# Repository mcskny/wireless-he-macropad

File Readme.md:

> **Separate transport profiles (experimental):** C6 0.1.6 and Studio 0.1.4 keep BLE and ESP-NOW layer settings separately, copying prior shared settings on first migration. Separate key assignments across mode switches were verified on the current hardware. Hall calibration remains shared.

> **6 November 2026:** Studio supports configuring C6 lighting, selecting layers and writing supported per-layer HID assignments over encrypted BLE. Hardware checks confirmed lighting changes on two layers and an H assignment that survived a C6 restart. Three paired-slot names are locally editable aliases, not automatically retrieved host names. BLE sensor telemetry and automatic synchronization between C6 and S3 are not implemented; a solid lighting color also persisted across a restart with Studio closed. Other hosts need further testing.

# Wireless HE Macropad

A wireless, 12-key Hall-effect macropad built around a custom PCB, an ESP32-C6 sender, an ESP32-S3 USB receiver, and a native macOS companion app.

The project explores analog key travel, configurable actuation, per-layer actions, responsive lighting, and power-conscious wireless operation. It is an **active hardware and firmware prototype**, not a finished commercial product.

## At a glance

- **12 analog Hall-effect keys**, arranged in three columns and four rows.
- A separate mechanical **layer button**, four layer indicator positions, and a rotary encoder in the design.
- **ESP32-C6 → ESP-NOW → ESP32-S3 → USB** for the current wireless test system.
- Direct **C6-to-host BLE HID** is integrated and keyboard output was confirmed on a Mac. Bond persistence and automatic reconnection still need a complete restart and mode-switch test.
- A custom PCB with DRV5055 sensors, a 16-channel multiplexer, and an external 12-bit ADC.
- Per-key lighting driven by a chain of 12 addressable LEDs.
- **Wireless HE Studio**, a native macOS app with live telemetry, calibration, interactive 2D/3D views, layers, and lighting controls.

## Gallery

<table>
<tr>
<td align="center"><br><b>Enclosure and layout</b></td>
<td align="center"><br><b>Custom PCB</b></td>
</tr>
<tr>
<td align="center"><br><b>Studio · layers and key assignments</b></td>
<td align="center"><br><b>Studio · lighting and 3D preview</b></td>
</tr>
</table>

The enclosure and PCB images are renders; Studio screenshots illustrate the interface and may not show its latest revision.

## How it works

Each key moves a magnet past a Hall sensor. The sensor's analog output is sampled and converted into a calibrated position, allowing the prototype to react to key travel rather than just an on/off switch.

```text
12 × DRV5055 sensors → CD74HC4067 multiplexer → MCP3202 ADC
                                                    │
                                           ESP32-C6 macropad
                                                    │ ESP-NOW
                                                    ▼
Mac / computer ← USB HID + serial telemetry ← ESP32-S3 dongle
        │                                           ▲
        └──── Studio configuration and live lighting ┘
```

The repository contains both the **current C6/S3 test bridge** and separate, evolving product-firmware projects. They are not interchangeable builds and do not necessarily use the same pin assignments.

## What works today

The following describes the test setup and the specific behavior observed, as of **5 November 2026**. A successful test of one action does not mean every combination has been validated.

| Area | Observed on the prototype | Still to do |
|---|---|---|
| Sensing | All 12 channels appeared in Studio; individual calibration, channel mapping, and live key movement were checked. | Long-run stability, cross-channel effects, physical travel measurement, and full calibration validation. |
| Wireless link | C6 → S3 → Mac telemetry works; Studio displays scan, submission, reception, and sequence-gap counters. | Reduce active-mode gaps, measure latency and range, and add authenticated pairing/encryption. |
| Direct BLE | C6 paired with a Mac and typed using a saved profile; Layer + KEY 0 switched transport and the transition effects were checked. | Validate persisted bonding across reboot and transport changes, BLE disconnect release, other hosts, latency, and power. |
| USB keyboard | Layer-specific keyboard actions and volume-down HID were tested on a Mac. A saved layer survived an S3 reconnect; output also worked with Studio closed. | More host/shortcut tests, disconnect recovery, and NKRO. The current keyboard report is 6KRO. |
| Hall behaviors | Rapid Trigger retriggering was tested with a partially released key. SOCD's last-pressed priority and return to the held key were also tested. | Wider sensitivity, multi-key, and long-duration hardware tests; two-stage behavior needs a physical test. |
| Lighting | All 12 LEDs lit. Live layer/effect synchronization, rainbow or snake color behavior, and virtual-key ripple triggering were checked. Sweep turn-off and ripple stopping were also checked physically. | Validate the complete effect set and persistence; lighting configuration is currently sent live rather than stored permanently on the device. |
| Power policy | Idle sensor scans and software-controlled MOSFET duty cycling were observed; the app displays commanded gate on-time. | Measure rail voltage, startup/settling, backfeed, actual current, and battery life. |
| Mac app | Live sensor values, 2D/3D views, layer controls, local profiles, and the device write path are available. Blender's move, rotate, and scale actions were tested. | Complete and validate all target-app actions, accessibility, long-term performance, and hardware integration. |
| Mechanical | A 3D model, PCB design, and enclosure renders exist. | Manufacture and validate the plate, case fit, and final assembly. |

The percentage in the graphic is a **manually reviewed, equally weighted checklist estimate**. Some items overlap; it is not a measurement of remaining work, reliability, or product readiness. See the [compact progress grid](Docs/progress/project-progress-grid-en.png) for the item index.

## Wireless HE Studio

Studio is a native **SwiftUI / AppKit / SceneKit** macOS application. Its current features include:

- A live ADC graph, raw channel diagnostics, channel remapping, per-key calibration, and idle-noise measurements.
- Interactive 2D and 3D views, key motion, and an exploded component view based on the project model.
- Four layers with keyboard/media actions, traditional thresholds, Rapid Trigger, SOCD, and local profile storage.
- Lighting previews and live control of effects such as static, breathing, wave, sweep, reactive, ripple, starlight, rainbow, and snake.
- Live rate and power-policy telemetry, including **commanded GPIO on-time** rather than a measured power figure.
- Turkish and English interface options, local backup, and sensor-session logs.

Studio includes 13 starter profiles covering creative applications and games. The 156 preset entries include direct mappings and suggested shortcuts that may need assignment in the target application; mapping and real application validation are distinct. The UI identifies these assignments. A mapped output does not prove the target application accepts it or that its shortcuts match the user's settings. Encoder actions and native analog gamepad output are not yet implemented end to end.

Studio writes supported actions for the **selected layer** to the S3. Calibration endpoints and supported Hall settings are included; local profile storage and device storage are distinct. Verify the target layer and assigned shortcuts before writing.

## Sampling and power experiments

The current test policy scans at **100 Hz while idle**, with a **1 kHz active target** after detected movement. Idle radio updates are targeted at 10 Hz without Studio or 100 Hz while Studio is connected; active transmission targets 1 kHz. The observed values in Studio are measurements, not guarantees of those targets.

In one active test the C6 reported roughly **983 scans/s** and **858 radio submissions/s**. These are short observations under specific conditions; submissions, received packets, and end-to-end input latency are different measurements. Sequence gaps can arise in scheduling, radio transmission, buffering, or USB.

With the experimental MOSFET build, the idle test showed approximately **13% commanded gate on-time**. Active-mode duty cycling with a 600 µs startup wait reduced a trial to about **620 scans/s**, so that experiment was reverted: the current active mode keeps the analog rail commanded on. GPIO timing does **not** establish the actual rail voltage, energy savings, or battery life. No power-saving multiplier is claimed.

## Hardware overview

| Component | Role |
|---|---|
| 12 × DRV5055A4 | Analog Hall sensors |
| CD74HC4067 | 16-channel analog multiplexer |
| MCP3202 | 12-bit external ADC |
| XIAO ESP32-C6 | Current wireless sender test board |
| ESP32-S3 | USB receiver and HID test board |
| 12 × SK6812MINI | Addressable key lighting |
| Mechanical switch | Layer button; current test wiring uses D7 to GND |
| Rotary encoder and four indicators | Designed controls; full hardware integration remains in progress |

The **test-bridge** C6 wiring uses D0–D3 for multiplexer selection, D4 for ADC chip select, D8–D10 for SPI, D6/GPIO16 for LED data, D5/GPIO23 for the optional active-low analog power gate, and D7/GPIO17 for the layer button. Check the [bridge documentation](examples/c6_s3_sensor_bridge/README.md), the actual board, and the schematic before connecting or powering anything. These pins are **not** a promise about the separate product firmware.

## Repository layout

| Path | Contents |
|---|---|
| [`Hardware/Kicad/`](Hardware/Kicad/) | PCB and schematic source files |
| [`Firmware/macropad-sender/`](Firmware/macropad-sender/) | Developing C6 product firmware |
| [`Firmware/dongle-receiver/`](Firmware/dongle-receiver/) | Developing S3 product firmware |
| [`Firmware/shared/`](Firmware/shared/) | Shared firmware modules and tests |
| [`examples/c6_s3_sensor_bridge/`](examples/c6_s3_sensor_bridge/) | Current C6/S3 wireless prototype and HID bridge |
| [`examples/c6_ble_hid_lab/`](examples/c6_ble_hid_lab/) | Isolated, buildable BLE HID transport experiment (separate from the integrated C6 build) |
| [`examples/macropad_12_idf/mac_app/`](examples/macropad_12_idf/mac_app/) | Wireless HE Studio macOS app |
| [`examples/lighting_espnow_lab/`](examples/lighting_espnow_lab/) | Lighting engine and protocol experiments |
| [`examples/crossover_analog/`](examples/crossover_analog/) | Earlier CrossOver analog-controller experiment |
| [`tools/progress.py`](tools/progress.py) | Generates the Turkish project progress map |

The earlier Assetto Corsa steering/throttle/brake experiment used a **wired sensor platform and a CrossOver virtual-controller bridge**. It does not demonstrate native analog gamepad output from the current S3 dongle.

## Build and test

The prototype firmware has been built with the project's **ESP-IDF 6.1** environment. The following examples build only; select the correct board, port, wiring, and configuration before flashing.

```sh
# C6 BLE + ESP-NOW test configuration
cd examples/c6_s3_sensor_bridge/c6
idf.py -B build-ble -D SDKCONFIG=sdkconfig.ble build
```

```sh
# S3 composite receiver — run from the repository root
cd examples/c6_s3_sensor_bridge/s3_composite
idf.py set-target esp32s3
idf.py build
```

The **experimental MOSFET build** uses a separate power configuration and requires the correct physical switching circuit; see the [bridge README](examples/c6_s3_sensor_bridge/README.md) before using it. The standard build should not be assumed to have the same gate configuration as the test board.

For the macOS app, see the [Studio README](examples/macropad_12_idf/mac_app/README.md). The current local build script targets macOS 26 and expects a configured ESP-IDF Python environment; it is not yet a signed, notarized general distribution.

## Known limitations

- ESP-NOW uses broadcast frames without authenticated encryption; CRC and source MAC checks do not authenticate senders. BLE encrypts links with bonded Just Works pairing, which does not provide MITM authentication.
- The S3 reports up to six ordinary keyboard keys at once; native analog gamepad output and physical encoder HID are unfinished.
- Some preset actions require explicit shortcut setup in the target program. Encoder presets and game-mode previews must not be mistaken for completed hardware behavior.
- The MOSFET status in Studio reports software commands. Actual sensor-rail behavior and power consumption still need electrical measurement.
- Hardware, firmware, app, and documentation are evolving; verify the specific test configuration before relying on a feature.

## Versioning and releases

C6 firmware, S3 firmware, and Studio use separate version numbers and GitHub releases. See [release notes](releases/CHANGELOG.md), [versions](releases/versions.json). Published tags are immutable. Initial releases are pre-releases; the Studio source currently has machine-specific runtime paths, so a portable binary is not claimed.

## License

This project is licensed under the [GNU General Public License, version 3](LICENSE) (GPL-3.0-only). Third-party components retain their own licenses.

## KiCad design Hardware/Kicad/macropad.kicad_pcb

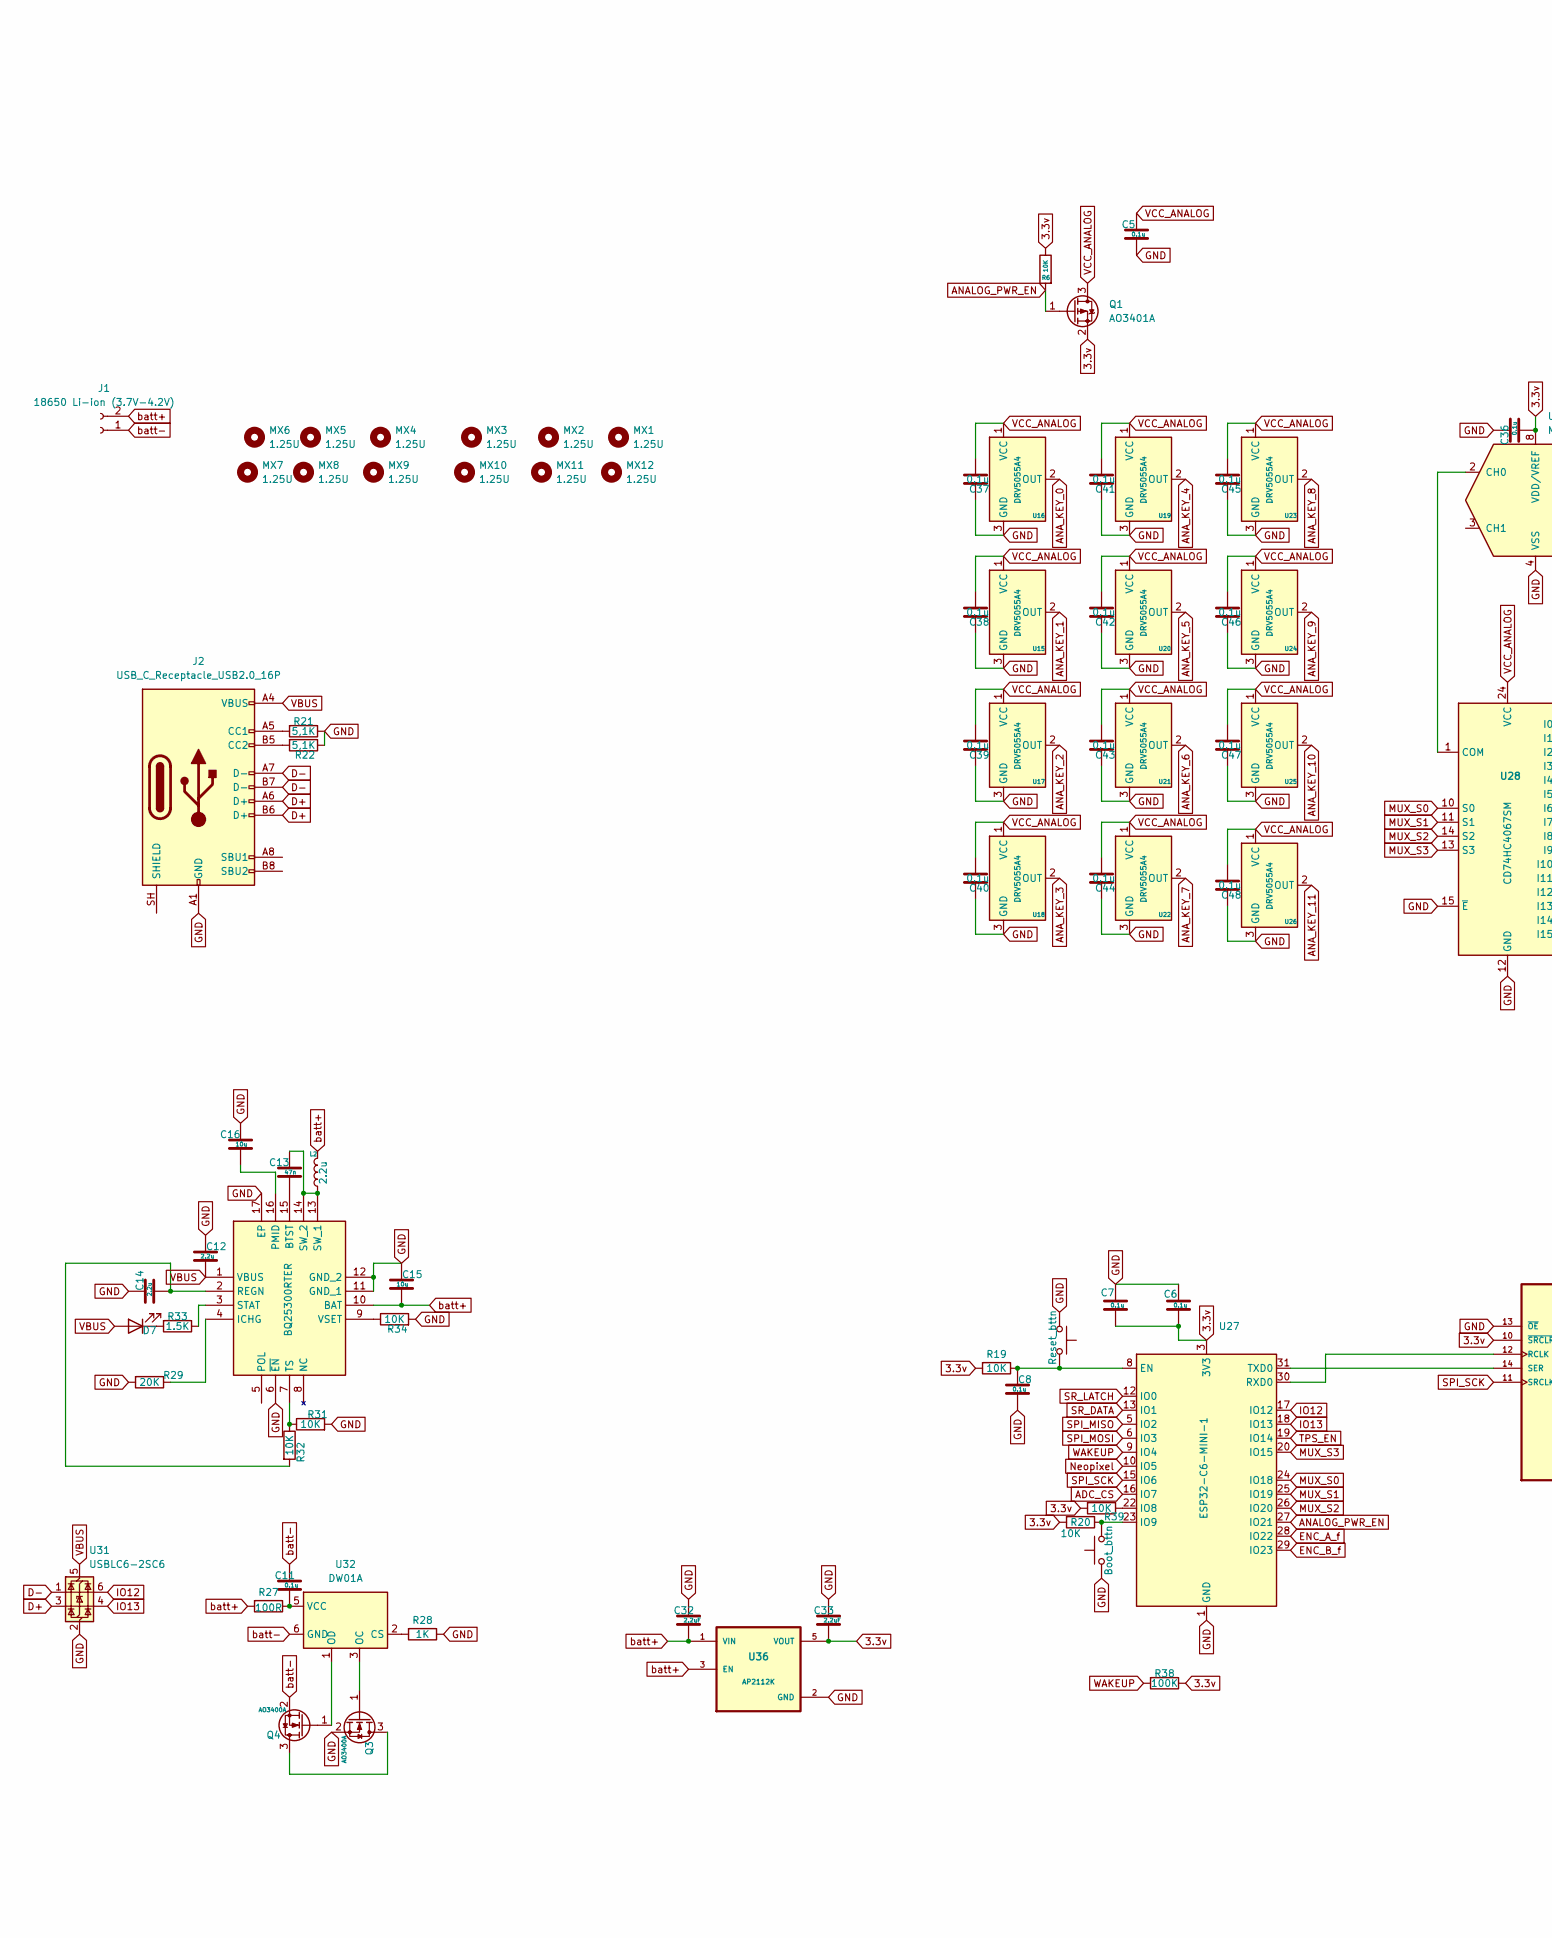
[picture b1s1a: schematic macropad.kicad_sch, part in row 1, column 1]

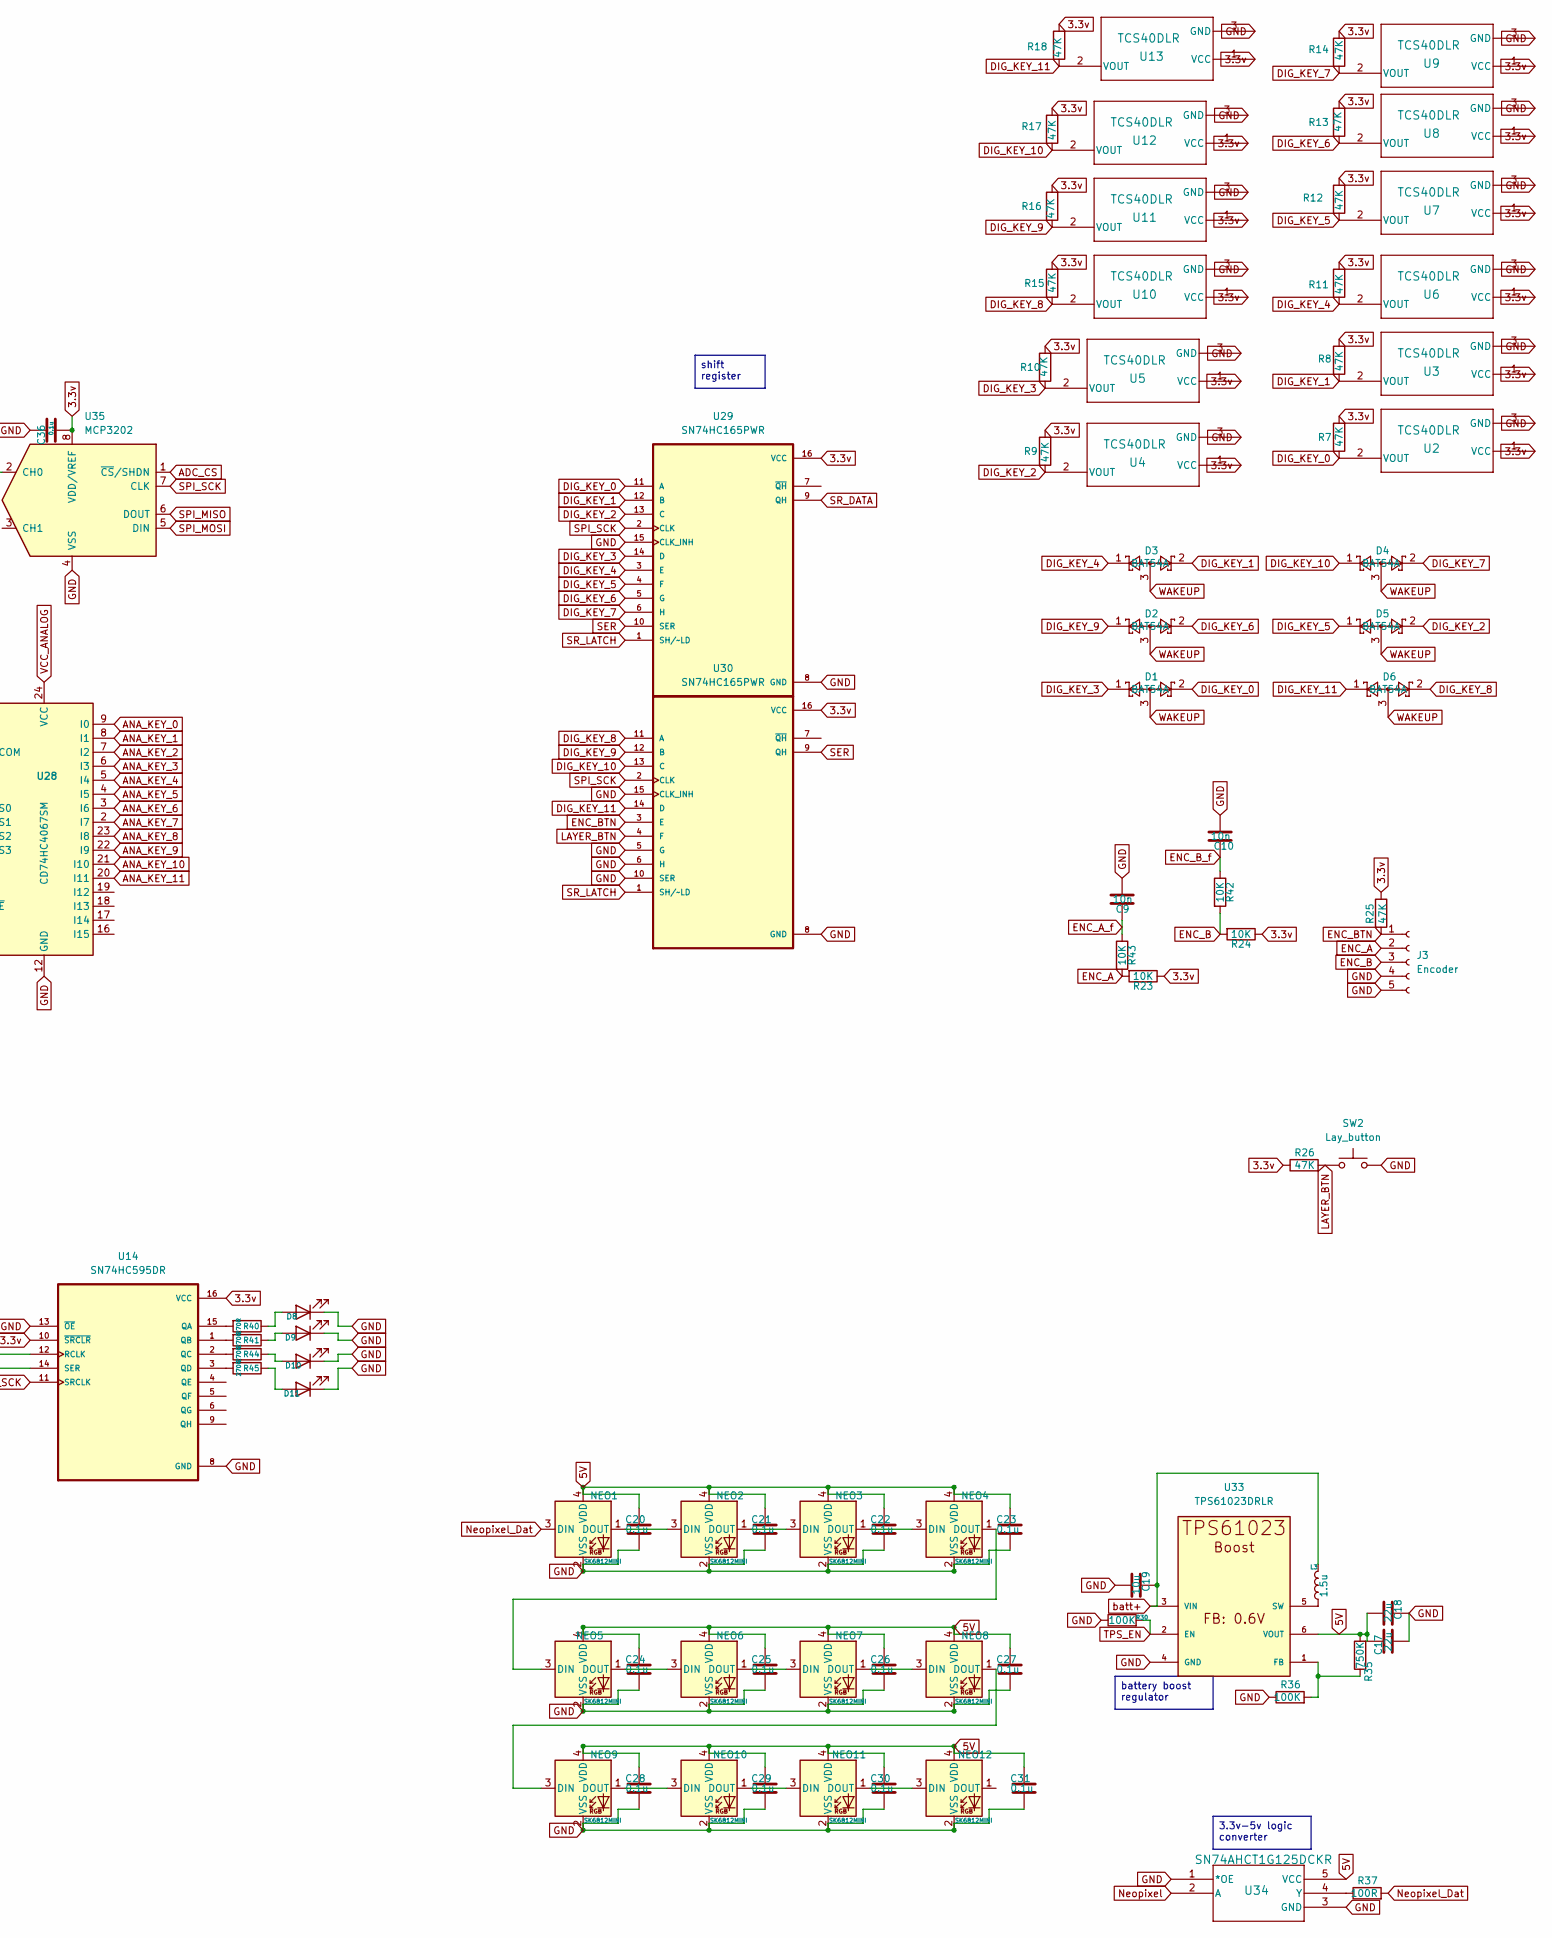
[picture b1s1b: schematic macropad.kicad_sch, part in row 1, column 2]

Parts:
C5, C6, C7, C8, C11, C20, C21, C22, C23, C24, C25, C26, C27, C28, C29, C30, C31, C36, C37, C38, C39, C40, C41, C42, C43, C44, C45, C46, C47, C48: 0.1u; C_0603_1608Metric_Pad1.08x0.95mm_HandSolder
C9, C10: 10n; C_0603_1608Metric_Pad1.08x0.95mm_HandSolder
C12, C14: 2.2u; C_0603_1608Metric_Pad1.08x0.95mm_HandSolder
C13: 47n; C_0603_1608Metric_Pad1.08x0.95mm_HandSolder
C15, C16: 10u; C_0805_2012Metric_Pad1.18x1.45mm_HandSolder
C17, C18: 22u; C_0603_1608Metric_Pad1.08x0.95mm_HandSolder
C19: 10u; C_0603_1608Metric_Pad1.08x0.95mm_HandSolder
C32, C33: 2.2uF; C_0603_1608Metric_Pad1.08x0.95mm_HandSolder
D1, D2, D3, D4, D5, D6: BAT54A; SOT-23_Handsoldering
D7, D8, D9, D10, D11: LED; LED_0603_1608Metric
J1: 18650 Li-ion (3.7V-4.2V); 648102131822
J2: USB_C_Receptacle_USB2.0_16P; USB_C_Receptacle_GCT_USB4110
J3: Encoder; SM04BPASS1TBTLFSN
L2: 2.2u; SRN4030HA2R2Y
L3: 1.5u; INDC2520X100N
MX1, MX2, MX3, MX4, MX5, MX6, MX7, MX8, MX9, MX10, MX11, MX12: 1.25U; switchsocket
NEO1, NEO2, NEO3, NEO4, NEO5, NEO6, NEO7, NEO8, NEO9, NEO10, NEO11, NEO12: SK6812MINI; LED_SK6812MINI_PLCC4_3.5x3.5mm_P1.75mm
Q1: AO3401A; SOT-23_Handsoldering
Q3, Q4: AO3400A; SOT-23
R6, R19, R20, R23, R24, R31, R32, R34, R39, R42, R43: 10K; R_0603_1608Metric_Pad0.98x0.95mm_HandSolder
R7, R8, R9, R10, R11, R12, R13, R14, R15, R16, R17, R18, R25, R26: 47K; R_0603_1608Metric_Pad0.98x0.95mm_HandSolder
R21, R22: 5,1K; R_0603_1608Metric_Pad0.98x0.95mm_HandSolder
R27, R37: 100R; R_0603_1608Metric_Pad0.98x0.95mm_HandSolder
R28: 1K; R_0603_1608Metric_Pad0.98x0.95mm_HandSolder
R29: 20K; R_0603_1608Metric_Pad0.98x0.95mm_HandSolder
R30, R36, R38: 100K; R_0603_1608Metric_Pad0.98x0.95mm_HandSolder
R33: 1.5K; R_0603_1608Metric_Pad0.98x0.95mm_HandSolder
R35: 750K; R_0603_1608Metric_Pad0.98x0.95mm_HandSolder
R40, R41, R44, R45: 270R; R_0603_1608Metric_Pad0.98x0.95mm_HandSolder
SW1: Boot_bttn; SW_Push_1P1T_NO_CK_KMR2
SW2: Lay_button; SW_Cherry_MX_1.00u_PCB
SW3: Reset_bttn; SW_Push_1P1T_NO_CK_KMR2
U2, U3, U4, U5, U6, U7, U8, U9, U10, U11, U12, U13: TCS40DLR; SOT-23_Handsoldering
U14: SN74HC595DR; SOIC127P600X175-16N
U15, U16, U17, U18, U19, U20, U21, U22, U23, U24, U25, U26: DRV5055A4; SOT-23_Handsoldering
U27: ESP32-C6-MINI-1
U28: CD74HC4067SM; SSOP-24_5.3x8.2mm_P0.65mm
U29, U30: SN74HC165PWR; SOP65P640X120-16N
U31: USBLC6-2SC6; SOT-23-6
U32: DW01A; SOT-23-6
U33: TPS61023DRLR; SOT563-ORI
U34: SN74AHCT1G125DCKR; DCK5
U35: MCP3202; SOIC-8_3.9x4.9mm_P1.27mm
U36: AP2112K; SOT95P285X140-5N; PARTREV 2-2
Z1: BQ25300RTER; QFN50P300X300X80-17N-D; Mouser Part Number 595-BQ25300RTER

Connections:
3.3v: C6.2, C7.2, C33.2, C36.2, Q1.2 (S), R6.1, R7.2, R8.2, R9.2, R10.2, R11.2, R12.2, R13.2, R14.2, R15.2, R16.2, R17.2, R18.2, R19.2, R20.2, R23.1, R24.1, R25.1, R26.1, R38.1, R39.2, U2.1 (VCC), U3.1 (VCC), U4.1 (VCC), U5.1 (VCC), U6.1 (VCC), U7.1 (VCC), U8.1 (VCC), U9.1 (VCC), U10.1 (VCC), U11.1 (VCC), U12.1 (VCC), U13.1 (VCC), U14.10 (~SRCLR), U14.16 (VCC), U27.3 (3V3), U29.16 (VCC), U30.16 (VCC), U35.8 (VDD/VREF), U36.5 (VOUT)
5V: C17.1, C18.2, C20.1, C21.1, C22.1, C23.1, C24.1, C25.1, C26.1, C27.1, C28.1, C29.1, C30.1, C31.1, NEO1.4 (VDD), NEO2.4 (VDD), NEO3.4 (VDD), NEO4.4 (VDD), NEO5.4 (VDD), NEO6.4 (VDD), NEO7.4 (VDD), NEO8.4 (VDD), NEO9.4 (VDD), NEO10.4 (VDD), NEO11.4 (VDD), NEO12.4 (VDD), R35.2, U33.6 (VOUT), U34.5 (VCC)
ADC_CS: U27.16 (IO7), U35.1 (~CS/SHDN)
ANALOG_PWR_EN: Q1.1 (G), R6.2, U27.27 (IO21)
ANA_KEY_0: U16.2 (OUT), U28.9 (I0)
ANA_KEY_1: U15.2 (OUT), U28.8 (I1)
ANA_KEY_2: U17.2 (OUT), U28.7 (I2)
ANA_KEY_3: U18.2 (OUT), U28.6 (I3)
ANA_KEY_4: U19.2 (OUT), U28.5 (I4)
ANA_KEY_5: U20.2 (OUT), U28.4 (I5)
ANA_KEY_6: U21.2 (OUT), U28.3 (I6)
ANA_KEY_7: U22.2 (OUT), U28.2 (I7)
ANA_KEY_8: U23.2 (OUT), U28.23 (I8)
ANA_KEY_9: U24.2 (OUT), U28.22 (I9)
ANA_KEY_10: U25.2 (OUT), U28.21 (I10)
ANA_KEY_11: U26.2 (OUT), U28.20 (I11)
D+: J2.A6 (D+), J2.B6 (D+), U31.3 (I/O2)
D-: J2.A7 (D-), J2.B7 (D-), U31.1 (I/O1)
DIG_KEY_0: D1.2, R7.1, U2.2 (VOUT), U29.11 (A)
DIG_KEY_1: D3.2, R8.1, U3.2 (VOUT), U29.12 (B)
DIG_KEY_2: D5.2, R9.1, U4.2 (VOUT), U29.13 (C)
DIG_KEY_3: D1.1, R10.1, U5.2 (VOUT), U29.14 (D)
DIG_KEY_4: D3.1, R11.1, U6.2 (VOUT), U29.3 (E)
DIG_KEY_5: D5.1, R12.1, U7.2 (VOUT), U29.4 (F)
DIG_KEY_6: D2.2, R13.1, U8.2 (VOUT), U29.5 (G)
DIG_KEY_7: D4.2, R14.1, U9.2 (VOUT), U29.6 (H)
DIG_KEY_8: D6.2, R15.1, U10.2 (VOUT), U30.11 (A)
DIG_KEY_9: D2.1, R16.1, U11.2 (VOUT), U30.12 (B)
DIG_KEY_10: D4.1, R17.1, U12.2 (VOUT), U30.13 (C)
DIG_KEY_11: D6.1, R18.1, U13.2 (VOUT), U30.14 (D)
ENC_A: J3.2, R23.2, R43.2
ENC_A_f: C9.1, R43.1, U27.28 (IO22)
ENC_B: J3.3, R24.2, R42.2
ENC_BTN: J3.1, R25.2, U30.3 (E)
ENC_B_f: C10.1, R42.1, U27.29 (IO23)
GND: C5.2, C6.1, C7.1, C8.1, C9.2, C10.2, C12.2, C14.2, C15.2, C16.2, C17.2, C18.1, C19.2, C20.2, C21.2, C22.2, C23.2, C24.2, C25.2, C26.2, C27.2, C28.2, C29.2, C30.2, C31.2, C32.1, C33.1, C36.1, C37.1, C38.1, C39.1, C40.1, C41.1, C42.1, C43.1, C44.1, C45.1, C46.1, C47.1, C48.1, D8.1 (K), D9.1 (K), D10.1 (K), D11.1 (K), J2.A1 (GND), J2.A12 (GND), J2.B1 (GND), J2.B12 (GND), J3.4, J3.5, NEO1.2 (VSS), NEO2.2 (VSS), NEO3.2 (VSS), NEO4.2 (VSS), NEO5.2 (VSS), NEO6.2 (VSS), NEO7.2 (VSS), NEO8.2 (VSS), NEO9.2 (VSS), NEO10.2 (VSS), NEO11.2 (VSS), NEO12.2 (VSS), Q3.2 (S), R21.1, R22.1, R28.1, R29.2, R30.1, R31.2, R34.2, R36.1, SW1.1, SW2.2, SW3.1, U2.3 (GND), U3.3 (GND), U4.3 (GND), U5.3 (GND), U6.3 (GND), U7.3 (GND), U8.3 (GND), U9.3 (GND), U10.3 (GND), U11.3 (GND), U12.3 (GND), U13.3 (GND), U14.8 (GND), U14.13 (~OE), U15.3 (GND), U16.3 (GND), U17.3 (GND), U18.3 (GND), U19.3 (GND), U20.3 (GND), U21.3 (GND), U22.3 (GND), U23.3 (GND), U24.3 (GND), U25.3 (GND), U26.3 (GND), U27.1 (GND), U27.2 (GND), U27.11 (GND), U27.14 (GND), U27.36 (GND), U27.37 (GND), U27.38 (GND), U27.39 (GND), U27.40 (GND), U27.41 (GND), U27.42 (GND), U27.43 (GND), U27.44 (GND), U27.45 (GND), U27.46 (GND), U27.47 (GND), U27.48 (GND), U27.49 (GND), U27.50 (GND), U27.51 (GND), U27.52 (GND), U27.53 (GND), U28.12 (GND), U28.15 (~E), U29.8 (GND), U29.15 (CLK_INH), U30.5 (G), U30.6 (H), U30.8 (GND), U30.10 (SER), U30.15 (CLK_INH), U31.2 (GND), U33.4 (GND), U34.1 (*OE), U34.3 (GND), U35.4 (VSS), U36.2 (GND), Z1.6 (~EN), Z1.11 (GND_1), Z1.12 (GND_2), Z1.17 (EP)
IO12: U27.17 (IO12), U31.6 (I/O1)
IO13: U27.18 (IO13), U31.4 (I/O2)
LAYER_BTN: R26.2, SW2.1, U30.4 (F)
MUX_S0: U27.24 (IO18), U28.10 (S0)
MUX_S1: U27.25 (IO19), U28.11 (S1)
MUX_S2: U27.26 (IO20), U28.14 (S2)
MUX_S3: U27.20 (IO15), U28.13 (S3)
Neopixel: U27.10 (IO5), U34.2 (A)
Neopixel_Dat: NEO1.3 (DIN), R37.2
unnamed: D7.1 (K), R33.2
unnamed: D8.2 (A), R40.1
unnamed: D9.2 (A), R41.1
unnamed: D10.2 (A), R44.1
unnamed: D11.2 (A), R45.1
unnamed: J2.A5 (CC1), R21.2
unnamed: J2.B5 (CC2), R22.2
unnamed: NEO1.1 (DOUT), NEO2.3 (DIN)
unnamed: NEO2.1 (DOUT), NEO3.3 (DIN)
unnamed: NEO3.1 (DOUT), NEO4.3 (DIN)
unnamed: NEO4.1 (DOUT), NEO5.3 (DIN)
unnamed: NEO5.1 (DOUT), NEO6.3 (DIN)
unnamed: NEO6.1 (DOUT), NEO7.3 (DIN)
unnamed: NEO7.1 (DOUT), NEO8.3 (DIN)
unnamed: NEO8.1 (DOUT), NEO9.3 (DIN)
unnamed: NEO9.1 (DOUT), NEO10.3 (DIN)
unnamed: NEO10.1 (DOUT), NEO11.3 (DIN)
unnamed: NEO11.1 (DOUT), NEO12.3 (DIN)
unnamed: Q3.3 (D), Q4.3 (D)
unnamed: Q3.1 (G), U32.3 (OC)
unnamed: Q4.1 (G), U32.1 (OD)
unnamed: R40.2, U14.15 (QA)
unnamed: R41.2, U14.1 (QB)
unnamed: R44.2, U14.2 (QC)
unnamed: R45.2, U14.3 (QD)
unnamed: U14.7 (QH), U14.9 (QH)
unnamed: U14.12 (RCLK), U27.30 (RXD0)
unnamed: U14.14 (SER), U27.31 (TXD0)
unnamed: C8.2, R19.1, SW3.2, U27.8 (EN)
unnamed: R39.1, U27.22 (IO8)
unnamed: R20.1, SW1.2, U27.23 (IO9)
unnamed: U28.1 (COM), U35.2 (CH0)
unnamed: R28.2, U32.2 (CS)
unnamed: C11.2, R27.1, U32.5 (VCC)
unnamed: R35.1, R36.2, U33.1 (FB)
unnamed: L3.1, U33.5 (SW)
unnamed: R37.1, U34.4 (Y)
unnamed: C13.1, Z1.15 (BTST)
unnamed: R29.1, Z1.4 (ICHG)
unnamed: C16.1, Z1.16 (PMID)
unnamed: C14.1, R32.2, Z1.2 (REGN)
unnamed: R33.1, Z1.3 (STAT)
unnamed: C13.2, L2.1, Z1.13 (SW_1), Z1.14 (SW_2)
unnamed: R31.1, R32.1, Z1.7 (TS)
unnamed: R34.1, Z1.9 (VSET)
SER: U29.10 (SER), U30.9 (QH)
SPI_MISO: U27.5 (IO2), U35.6 (DOUT)
SPI_MOSI: U27.6 (IO3), U35.5 (DIN)
SPI_SCK: U14.11 (SRCLK), U27.15 (IO6), U29.2 (CLK), U30.2 (CLK), U35.7 (CLK)
SR_DATA: U27.13 (IO1), U29.9 (QH)
SR_LATCH: U27.12 (IO0), U29.1 (SH/~LD), U30.1 (SH/~LD)
TPS_EN: R30.2, U27.19 (IO14), U33.2 (EN)
VBUS: C12.1, D7.2 (A), J2.A4 (VBUS), J2.A9 (VBUS), J2.B4 (VBUS), J2.B9 (VBUS), U31.5 (VBUS), Z1.1 (VBUS)
VCC_ANALOG: C5.1, C37.2, C38.2, C39.2, C40.2, C41.2, C42.2, C43.2, C44.2, C45.2, C46.2, C47.2, C48.2, Q1.3 (D), U15.1 (VCC), U16.1 (VCC), U17.1 (VCC), U18.1 (VCC), U19.1 (VCC), U20.1 (VCC), U21.1 (VCC), U22.1 (VCC), U23.1 (VCC), U24.1 (VCC), U25.1 (VCC), U26.1 (VCC), U28.24 (VCC)
WAKEUP: D1.3, D2.3, D3.3, D4.3, D5.3, D6.3, R38.2, U27.9 (IO4)
batt+: C15.1, C19.1, C32.2, J1.2, L2.2, L3.2, R27.2, U33.3 (VIN), U36.1 (VIN), U36.3 (EN), Z1.10 (BAT)
batt-: C11.1, J1.1, Q4.2 (S), U32.6 (GND)

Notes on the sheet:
3.3v-5v logic converter
battery boost regulator
shift register

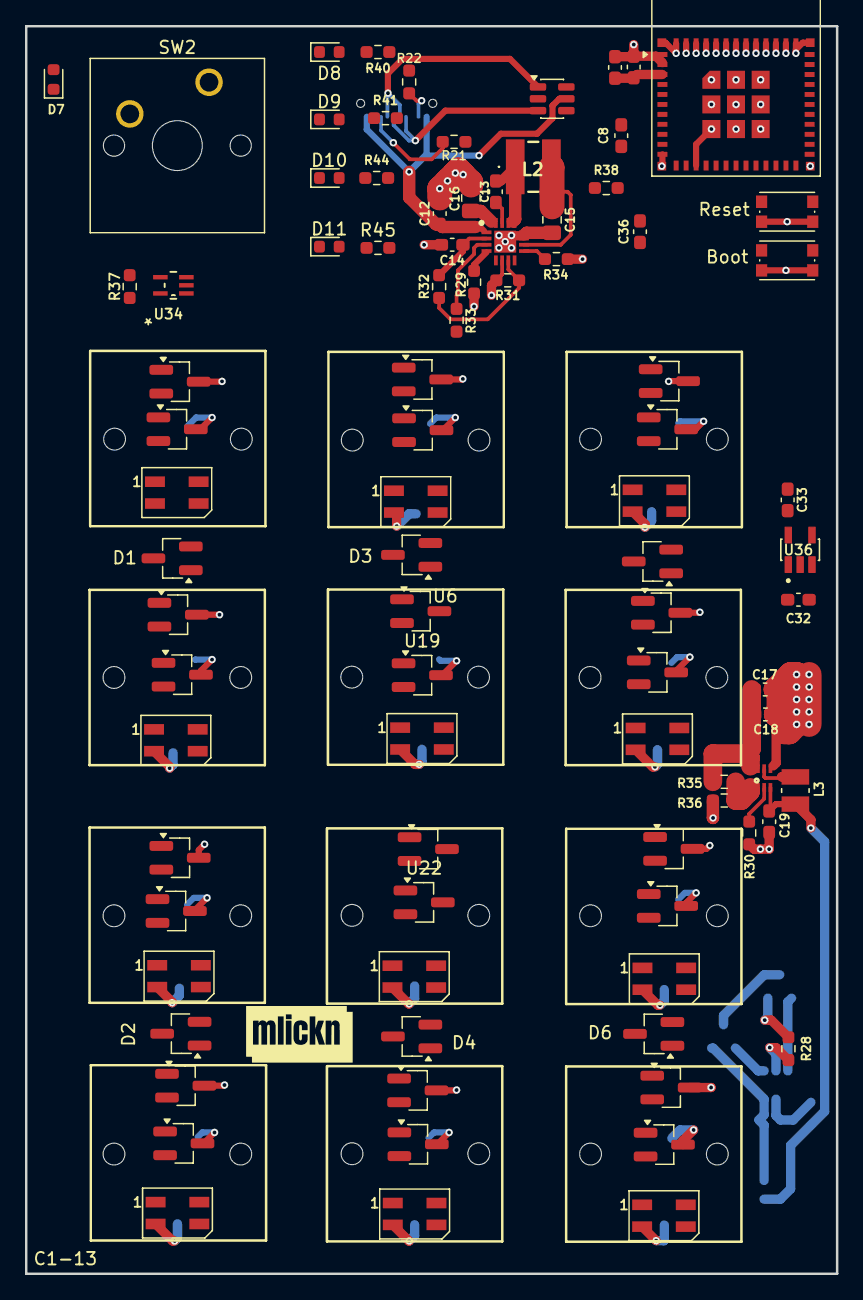
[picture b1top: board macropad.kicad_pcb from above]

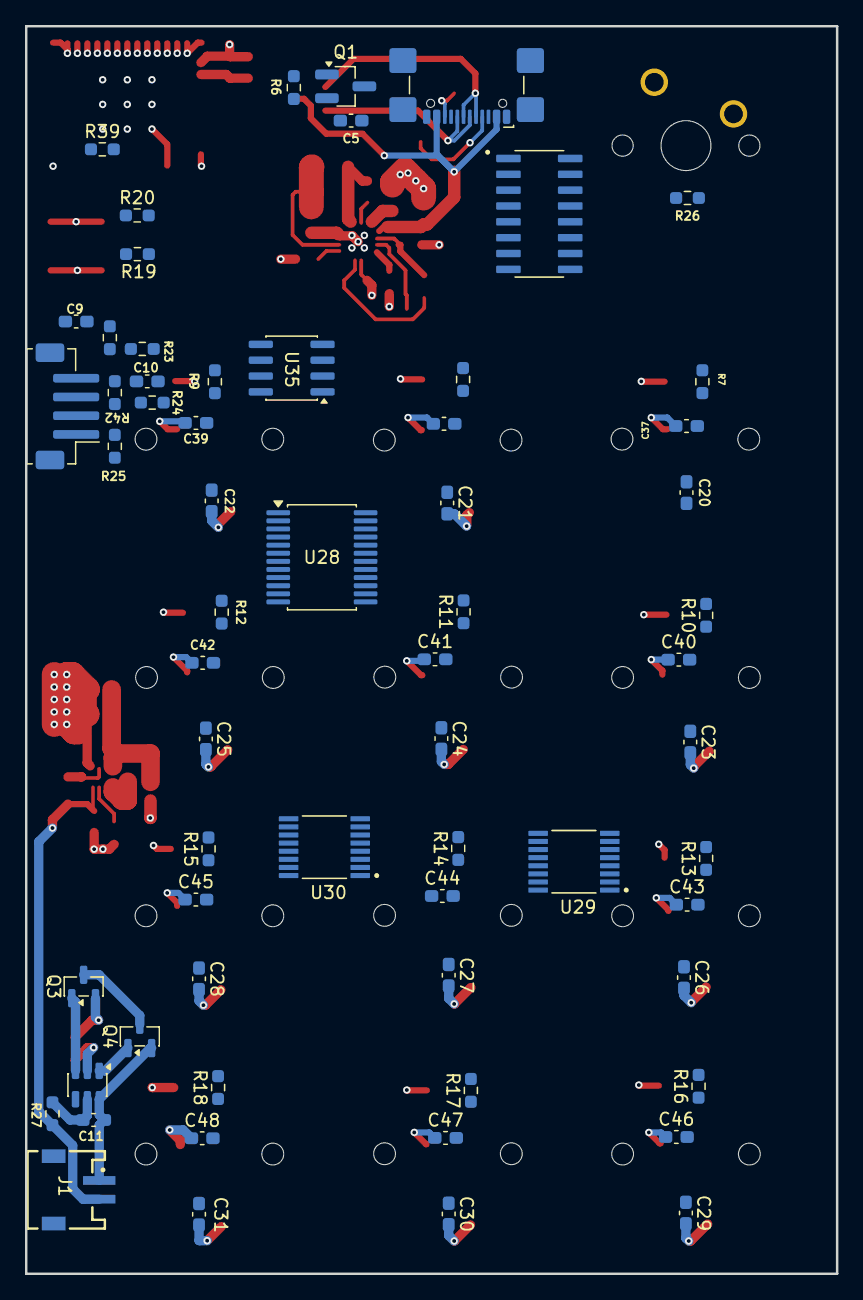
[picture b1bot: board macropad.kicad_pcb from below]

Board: 4 copper layers, 65.0 x 100.0 mm, 164 parts (63 on the bottom side), 102 nets.

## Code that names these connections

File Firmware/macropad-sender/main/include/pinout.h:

// SPDX-License-Identifier: GPL-3.0-only
// Copyright (c) 2026 ESP32-C6 Macropad. All rights reserved.

/**
 * @file pinout.h
 * @brief ESP32-C6-MINI-1 donanım pin atamalarının tek kaynağı (single source of truth).
 *
 * Bu dosya projedeki TUM GPIO atamalarini icerir. Baska bir .c/.h dosyasinda
 * somut pin numarasi KULLANILMAMALIDIR; tum bilesenler pin numaralarini
 * init fonksiyonlari uzerinden main.c tarafindan alir.
 *
 * Kaynak: pcb_pinler.md (Hall Effect Macropad pin haritasi).
 *
 * Onemli notlar:
 *  - RXD0 (GPIO30) ve TXD0 (GPIO31) UART0 pinleri LED shift register'a
 *    ayrilmistir. Bu nedenle log cikisi USB-CDC uzerinden yapilir
 *    (bkz. sdkconfig.defaults: CONFIG_ESP_CONSOLE_USB_CDC=y).
 *  - IO8 ve IO9 strapping pinleridir; firmware'de kullanilmaz.
 *  - IO12/IO13 USB D+/D- pinleridir; USB peripheral tarafindan yonetilir,
 *    manuel GPIO yapilandirmasi gerektirmez.
 *  - VBUS ve /CHG sinyallerinin pin routing'i henuz netlesmedigi icin
 *    -1 (stub) olarak tanimlanmistir; charger_if bileseni bu durumu soyutlar.
 *  - SW2 (Layer Butonu) ve ENC_BTN direk GPIO DEGILDIR; U30 (SN74HC165)
 *    shift register'inin E/F pinlerinden okunur (bkz. shift_in_sn74hc165).
 *  - Diot-OR hatti (IO4 WAKEUP) yalnizca 12 dijital tusun OR'lanmis halidir.
 *    Encoder ve SR uzerinden okunan butonlar bu hatta bagli degildir.
 */
#pragma once

#ifdef __cplusplus
extern "C" {
#endif

/* =========================================================================
 * SPI bus (MCP3202 ADC icin donanimsal SPI)
 * Not: SCK (IO6) SN74HC165 ve 74HC595 shift register'lariyla ORTAKTIR.
 *       SR'lar bit-banging ile surulurken ayni SCK pini kullanilir.
 * ========================================================================= */
#define PIN_SPI_SCK          (6)    ///< U35 (ADC) + U29/U30 (dijital tus SR) + U14 (LED SR) ortak clock
#define PIN_SPI_MISO         (2)    ///< U35 ADC DOUT (analog okuma)
#define PIN_SPI_MOSI         (3)    ///< U35 ADC DIN
#define PIN_ADC_CS           (7)    ///< U35 ~CS (MCP3202)

/* =========================================================================
 * Dijital Tus Shift Register (SN74HC165 x2, bit-bang)
 * PCB'de iki adet SN74HC165, toplam 16 bit okunur.
 * ========================================================================= */
#define PIN_SR_LATCH         (0)    ///< U29/U30 SH/~LD (latch / ornekleme)
#define PIN_SR_DATA          (1)    ///< U29 QH (seri veri cikisi), 16 bit shift-in

/* =========================================================================
 * LED Shift Register (74HC595, bit-bang)
 * Durum/layer LED'leri D8-D11 icin. SCK ortak (PIN_SPI_SCK).
 * ========================================================================= */
#define PIN_LED_SR_RCLK      (30)   ///< U14 RCLK (latch) — RXD0 pininin GPIO kullanimi
#define PIN_LED_SR_SER       (31)   ///< U14 SER (seri veri) — TXD0 pininin GPIO kullanimi

/* =========================================================================
 * Analog Coklayici (CD74HC4067)
 * S0-S3 ile 0-15 arasi kanal secilir. Kullanilan: ANA_KEY_0..11 (kanal 0-11).
 * Kanal 12-15: pil voltaj boleni / /CHG gibi ek sinyaller icin reserve.
 * ========================================================================= */
#define PIN_MUX_S0           (18)
#define PIN_MUX_S1           (19)
#define PIN_MUX_S2           (20)
#define PIN_MUX_S3           (15)
#define MUX_CHANNEL_ANALOG_KEY_COUNT  (12)  ///< ANA_KEY_0..11
#define MUX_CHANNEL_BATTERY           (12)  ///< Pil voltaj boleni (stub; donanim netlesince guncellenecek)
#define MUX_CHANNEL_CHG_STAT          (13)  ///< /CHG sinyali (stub; donanim netlesince guncellenecek)

/* =========================================================================
 * Guc Kontrolu
 * ========================================================================= */
#define PIN_TPS_EN           (14)   ///< U33 boost regulator enable (5V_LED hatti — LED'ler icin)
#define PIN_ANALOG_PWR_EN    (21)   ///< Q1 (P-FET) gate — analog Hall sensörleri + mux gucu (pil tasarrufu)

/* =========================================================================
 * Neopixel (SK6812MINI, 12 LED daisy-chain)
 * ========================================================================= */
#define PIN_NEOPIXEL_DATA    (5)    ///< U34 level shifter uzerinden NEO1-12
#define NEOPIXEL_LED_COUNT   (12)

/* =========================================================================
 * Encoder (donanimsal PCNT)
 * ========================================================================= */
#define PIN_ENC_A            (22)   ///< Filtrelenmis (R43/C9)
#define PIN_ENC_B            (23)   ///< Filtrelenmis (R42/C10)
/* ENC_BTN ve SW2 direk GPIO DEGILDIR; U30 SN74HC165 E/F pinlerinden okunur.
 * Bu sabitler yalnizca SR okuma sonrasi bit konumlarini belirtmek icin kullanilir
 * (bkz. shift_in_sn74hc165.h). */

/* =========================================================================
 * Wake-up (Diot-OR hatti)
 * Yalnizca 12 dijital tusun OR'lanmis halidir. Encoder/SR butonlari haric.
 * ========================================================================= */
#define PIN_WAKEUP_DIOT_OR   (4)    ///< Diot-OR cikisi — GPIO wake (light/deep sleep)

/* =========================================================================
 * Strapping pinler (KULLANMA)
 * ========================================================================= */
#define PIN_BOOT_BTN         (9)    ///< SW1 BOOT butonu — strapping, genel amacli I/O olarak KULLANMA
#define PIN_STRAPPING_IO8    (8)    ///< R39 pull-up, strapping — bosta/kullanma

/* =========================================================================
 * USB (donanimsal, GPIO yapilandirmasi YOK)
 * ========================================================================= */
/* IO12/IO13 USB D+/D- — USB peripheral otomatik yonetir, firmware'de manuel
 * pin ayari yapilmasina gerek yoktur. */

/* =========================================================================
 * Sarj sensörleri (STUB — donanim routing'i henuz netlesmedi)
 * Bu pinler -1 olarak birakilmistir; charger_if bileseni bu durumu soyutlar.
 * Donanim karari netlesince sadece bu sabitler guncellenecektir.
 * ========================================================================= */
#define PIN_VBUS_SENSE       (-1)   ///< STUB: VBUS (USB takili) tespiti, henuz pin atanmadi
#define PIN_CHG_STAT         (-1)   ///< STUB: /CHG (bq253000rter STAT) sinyali, henuz pin atanmadi

/* =========================================================================
 * SPI donanimsal birim secimi
 * ESP32-C6'da 2 adet SPI host var: SPI1 (flash icin rezerve), SPI2 (GPSPI).
 * MCP3202 icin SPI2 (ESP_GSPI_HOST) kullanilir.
 * ========================================================================= */
#define MCP3202_SPI_HOST     (SPI2_HOST)
#define MCP3202_SPI_CLOCK_HZ (1000000)  ///< 1 MHz (MCP3202 max 3.2V'da 1 MHz, 5V'da 2 MHz)

#ifdef __cplusplus
}
#endif

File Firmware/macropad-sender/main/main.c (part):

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    if (state->config.active_layer > 3) state->config.active_layer = 0;

    /* 2. SPI bus + cevresel */
    ESP_RETURN_ON_ERROR(spi_bus_init(PIN_SPI_SCK), TAG, "spi_bus");
    ESP_RETURN_ON_ERROR(mcp3202_init(PIN_ADC_CS, PIN_SPI_MISO, PIN_SPI_MOSI), TAG, "mcp3202");
    ESP_RETURN_ON_ERROR(mux_cd74hc4067_init(PIN_MUX_S0, PIN_MUX_S1, PIN_MUX_S2, PIN_MUX_S3), TAG, "mux");
    ESP_RETURN_ON_ERROR(shift_in_sn74hc165_init(PIN_SR_LATCH, PIN_SR_DATA, SHIFT_IN_BITS), TAG, "shift_in");
    ESP_RETURN_ON_ERROR(shift_out_74hc595_init(PIN_LED_SR_RCLK, PIN_LED_SR_SER, SHIFT_OUT_BITS), TAG, "shift_out");

    /* 3. Encoder */
    ESP_RETURN_ON_ERROR(encoder_init(PIN_ENC_A, PIN_ENC_B), TAG, "encoder");

    /* 4. Neopixel + power */
    ESP_RETURN_ON_ERROR(neopixel_init(PIN_NEOPIXEL_DATA, NEOPIXEL_LED_COUNT), TAG, "neopixel");
    ESP_RETURN_ON_ERROR(power_ctrl_init(PIN_ANALOG_PWR_EN, PIN_TPS_EN), TAG, "power_ctrl");

    /* 5. Battery + charger */
    battery_init();
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        TAG, "espnow_link");

    /* 7. Wakeup manager */
    ESP_RETURN_ON_ERROR(wakeup_manager_init(PIN_WAKEUP_DIOT_OR, true), TAG, "wakeup");

    /* Runtime state (Bölüm 1.1) */
    state->link.is_connected_to_s3 = true;
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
